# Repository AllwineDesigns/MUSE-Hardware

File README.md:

Hardware files for MUSE - Music Using Simple Electronics

The hardware is released under [Creative Commons Attribution-ShareAlike 4.0 International](https://creativecommons.org/licenses/by-sa/4.0/).

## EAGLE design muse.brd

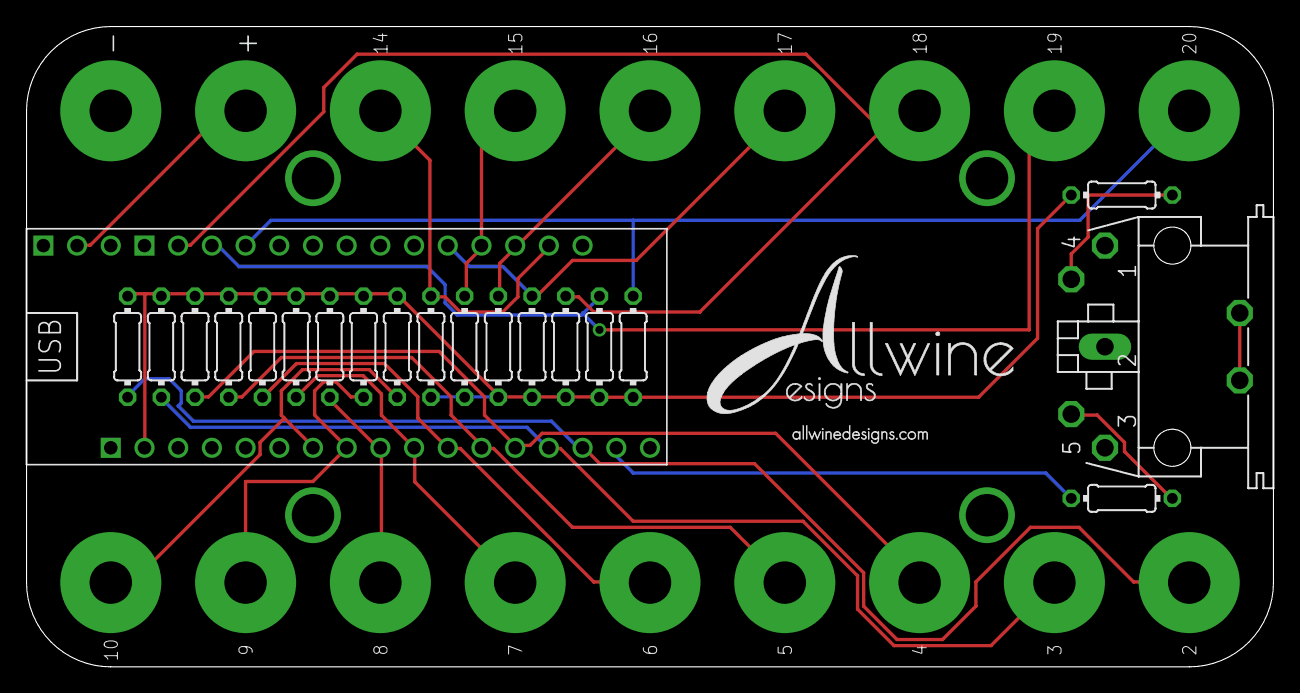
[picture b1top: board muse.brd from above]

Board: 2 copper layers, 94.0 x 48.3 mm, 22 parts (0 on the bottom side), 23 nets.

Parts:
R1, R2, R3, R4, R5, R6, R7, R8, R9, R14, R15, R16, R17, R18, R19, R20: 22M; 0204/7
R12, R13: 220; 0204/7
U$1: POLOLU_A_STAR_32U4_MINI
U$2, U$3: 3MM_1X9_CONNECTOR
X1: MAB5SH

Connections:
GND: U$1.BAT_MINUS, U$1.GND, U$1.GND2, U$3.P1, X1.2
unnamed: R1.1, U$1.2, U$2.P9
unnamed: R2.1, U$1.3, U$2.P8
unnamed: R3.1, U$1.4, U$2.P7
unnamed: R4.1, U$1.5, U$2.P6
unnamed: R5.1, U$1.6, U$2.P5
unnamed: R6.1, U$1.7, U$2.P4
unnamed: R7.1, U$1.8, U$2.P3
unnamed: R8.1, U$1.9, U$2.P2
unnamed: R9.1, U$1.10, U$2.P1
unnamed: R12.2, X1.4
unnamed: U$1.BAT_PLUS, U$3.P2
unnamed: R13.2, U$1.1
unnamed: R13.1, X1.5
unnamed: R14.2, U$1.MISO, U$3.P3
unnamed: R15.2, U$1.SCK, U$3.P4
unnamed: R16.2, U$1.MOSI, U$3.P5
unnamed: R17.2, U$1.RXL, U$3.P6
unnamed: R18.2, U$1.A0, U$3.P7
unnamed: R19.2, U$1.A1, U$3.P8
unnamed: R20.2, U$1.A2, U$3.P9
PE: X1.PE, X1.PE@
VCC: R1.2, R2.2, R3.2, R4.2, R5.2, R6.2, R7.2, R8.2, R9.2, R12.1, R14.1, R15.1, R16.1, R17.1, R18.1, R19.1, R20.1, U$1.5V

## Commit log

2016-10-23 first check in
2016-11-08 added TODO
2017-01-17 routed pin 4 of midi connector
